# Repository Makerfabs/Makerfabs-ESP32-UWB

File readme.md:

# Makerfabs ESP32 UWB & Display

```c++
/*
Version:		V4.3
Author:			Vincent
Create Date:	2021/11/6
Note:
	2021/12/9 	V2.0:Add a Indoor Positioning demo.
	2022/6/29 	V2.1:Add DW3000 library.
	2022/8/1  	V3.0:Provides a library available for high-power versions. Move DW3000 to other 		  					     repositories.
	2022/9/6	V3.1:Added changes to the high-power version.
	2022/10/26 	V4.0:Add new version with SSD1306
	2022/11/15	V4.1:Change library name to mf_DW1000.zip
	2022/12/29	V4.2: Change wiki link
	2023/1/3	V4.3: Change directory name.
*/
```

[toc]

# Makerfabs

[Makerfabs home page](https://www.makerfabs.com/)

[Makerfabs Wiki](https://wiki.makerfabs.com/)

# Makerfabs ESP32 UWB Serials
## Intruduce

ESP32 UWB : [esp32-uwb-ultra-wideband](https://www.makerfabs.com/esp32-uwb-ultra-wideband.html) 

ESP32 UWB Pro : [esp32-uwb-high-power](https://www.makerfabs.com/esp32-uwb-high-power-120m.html)

ESP32 UWB Pro with Display : [ESP32 UWB Pro with Display](https://www.makerfabs.com/esp32-uwb-pro-with-display.html)

Wiki Link : [ESP32 UWB Pro with Display](https://wiki.makerfabs.com/ESP32_UWB_Pro_with_Display.html) 

Ultra-wideband (UWB) is a short-range, wireless communication protocol that operates through radio waves, enables secure reliable ranging and precision sensing, creating a new dimension of spatial context for wireless devices.

This new ESP32 UWB pro with display is the updated version of ESP32 UWB Pro, with the following new spec:

- On-board OLED, 1.3” 128*64, so the distance results can be directly displayed
- Lipo battery charger& connector, so this module can work separately with batteries
- Update UWB position, so the module can be directly installed into a case

| | **UWB Basic** | **UWB Pro** | **UWB Pro with Display** | **UWB DW3000** |
| --------------------- | ------------------------------------------------------------ | ------------------------------------------------------------ | ------------------------ | ------------------------------------------------------------ |
| CPU                   | ESP32-WROOM/WROVER                                           | ESP32-WROVER                                                 | ESP32-WROVER             | ESP32-WROOM/WROVER                                           |
| Core UWB              | DW1000                                                       | DW1000                                                       | DW1000                   | DW3000                                                       |
| Screen                | N                                                            | N                                                            | Y                        | N                                                            |
| Measuring distance(m) | 45                                                           | 200                                                          | 200                      | 20                                                           |
| Battery Socket        | N                                                            | N                                                            | Y                        | N                                                            |
| UWB Channel           | 2/5                                                          | 2/5                                                          | 2/5                      | 5/9                                                          |
| Apple Interoperable   | N                                                            | N                                                            | N                        | Y                                                            |
| Suitable for          | Normal Testing                                               | Long distance needed                                         | Long distance needed     | Product development                                          |

### UWB Basic

### UWB Pro

### UWB Pro with Display

# Example

## Compiler Options

**If you have any questions，such as how to install the development board, how to download the code, how to install the library. Please refer to :[Makerfabs_FAQ](https://github.com/Makerfabs/Makerfabs_FAQ)**

- Install board : ESP32 .
- Rename mf_DW1000.zip to DW1000.zip and install it.
- Install library : Adafruit_SSD1306
- Upload code, select board "ESP32 DEV"

**This library was modified from the [DW1000](https://github.com/thotro/arduino-dw1000) library to work with the Makerfabs hardware. **

**Please download the latest version from our Github.**

## Example List

### uwb_tag

*For ESP32 UWB and ESP32 UWB Pro*

Distance to the receiving end of the test. You need an anchor point to receive data.

### uwb_tag_display

*For ESP32 UWB Pro with display*

Distance to the receiving end of the test. You need an anchor point to receive data.

### anchor

*For ESP32 UWB and ESP32 UWB Pro*

Distance test anchor point.

### anchor_display

*For ESP32 UWB Pro with display*

Distance test anchor point.

### Indoor positioning

*For ESP32 UWB and ESP32 UWB Pro*

Three UWB modules were used for indoor plane positioning. Data is transmitted through UDP protocol and graphically displayed in Python. 

The law of cosines is used to calculate tag coordinates.

```python
def tag_pos(a, b, c):
    # p = (a + b + c) / 2.0
    # s = cmath.sqrt(p * (p - a) * (p - b) * (p - c))
    # y = 2.0 * s / c
    # x = cmath.sqrt(b * b - y * y)
    cos_a = (b * b + c*c - a * a) / (2 * b * c)
    x = b * cos_a
    y = b * cmath.sqrt(1 - cos_a * cos_a)

    return round(x.real, 1), round(y.real, 1)
```

## Pin Define

### ESP32 UWB and ESP32 UWB Pro

```c++
#define SPI_SCK 18
#define SPI_MISO 19
#define SPI_MOSI 23

#define DW_CS 4
#define PIN_RST 27
#define PIN_IRQ 34
```

### ESP32 Pro with display

```c++
#define SPI_SCK 18
#define SPI_MISO 19
#define SPI_MOSI 23

#define UWB_SS 21   // spi select pin
#define UWB_RST 27  // reset pin
#define UWB_IRQ 34  // irq pin

#define I2C_SDA 4	//I2C screen ssd1306
#define I2C_SCL 5
```

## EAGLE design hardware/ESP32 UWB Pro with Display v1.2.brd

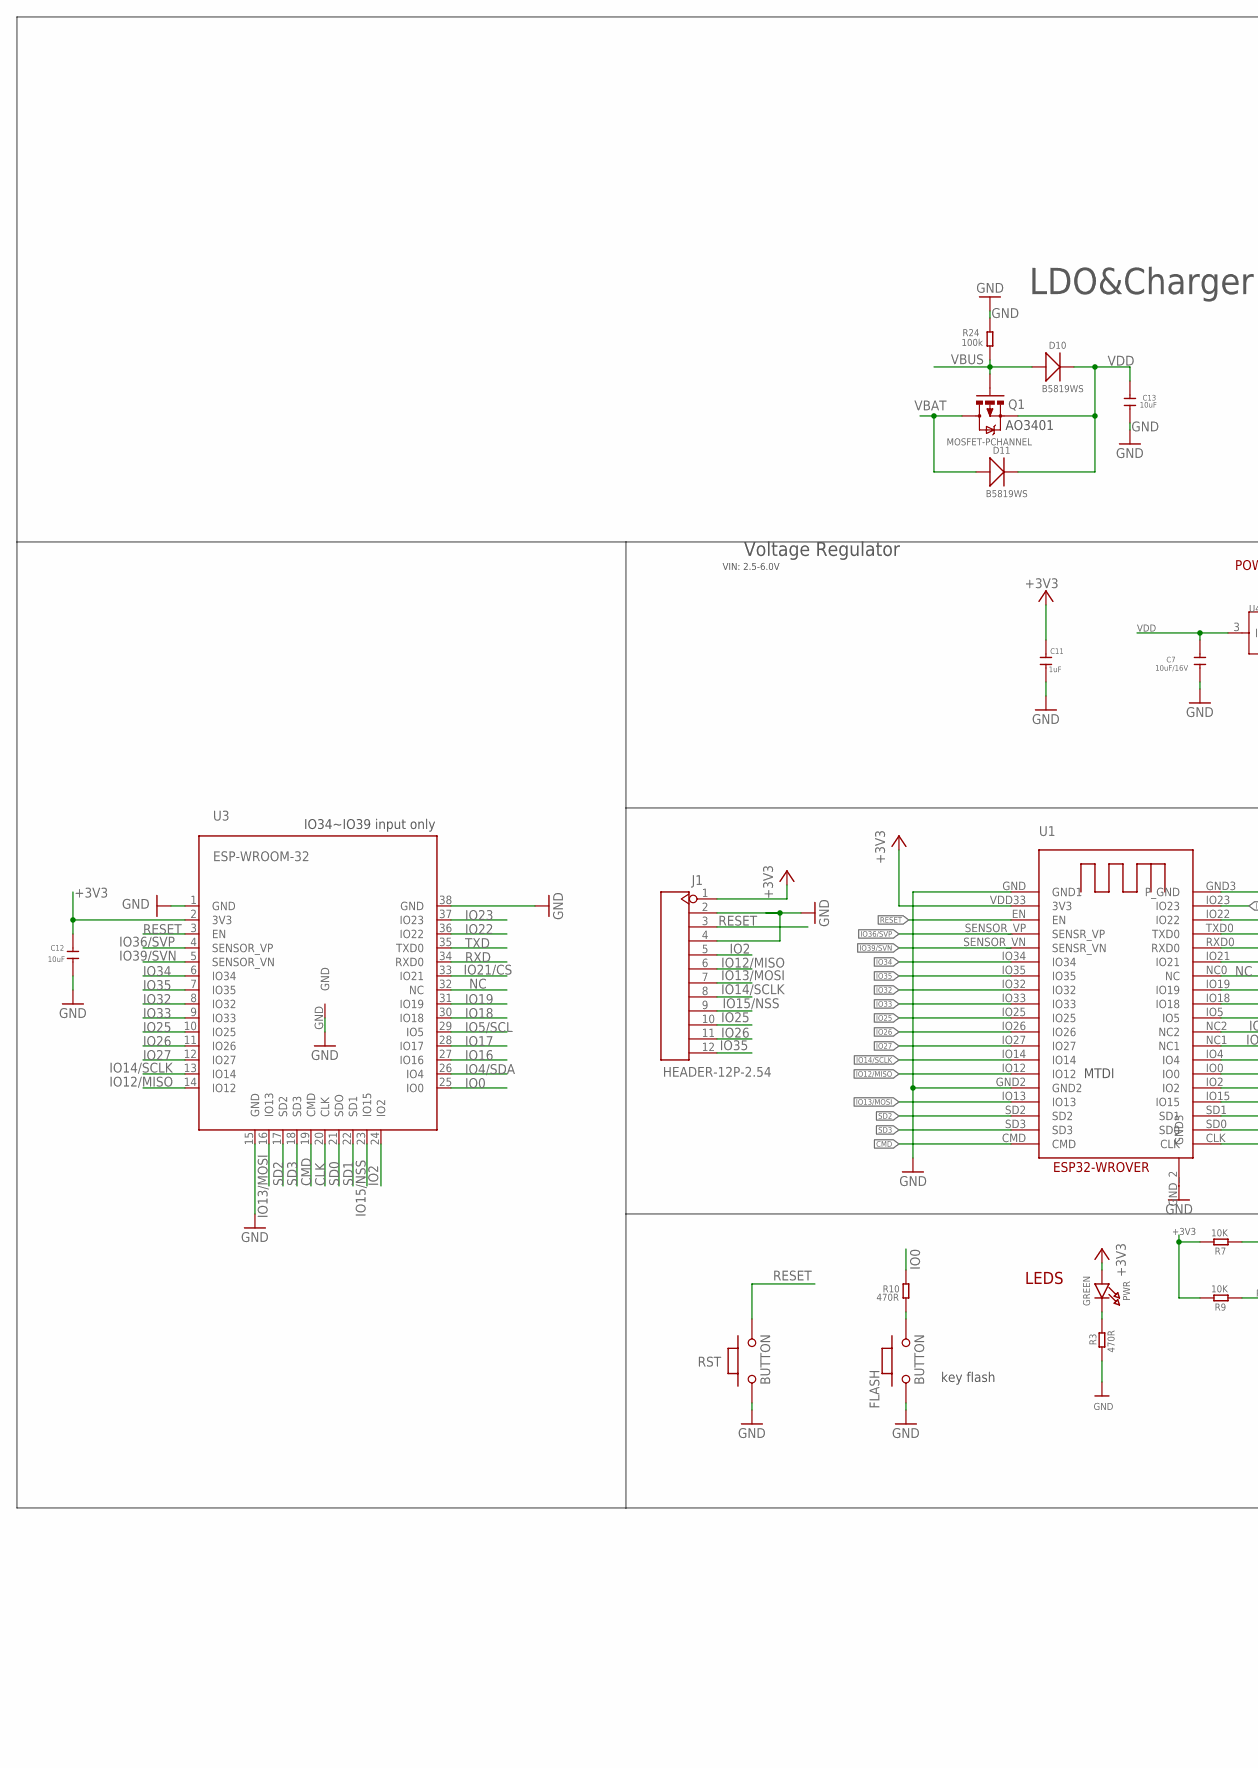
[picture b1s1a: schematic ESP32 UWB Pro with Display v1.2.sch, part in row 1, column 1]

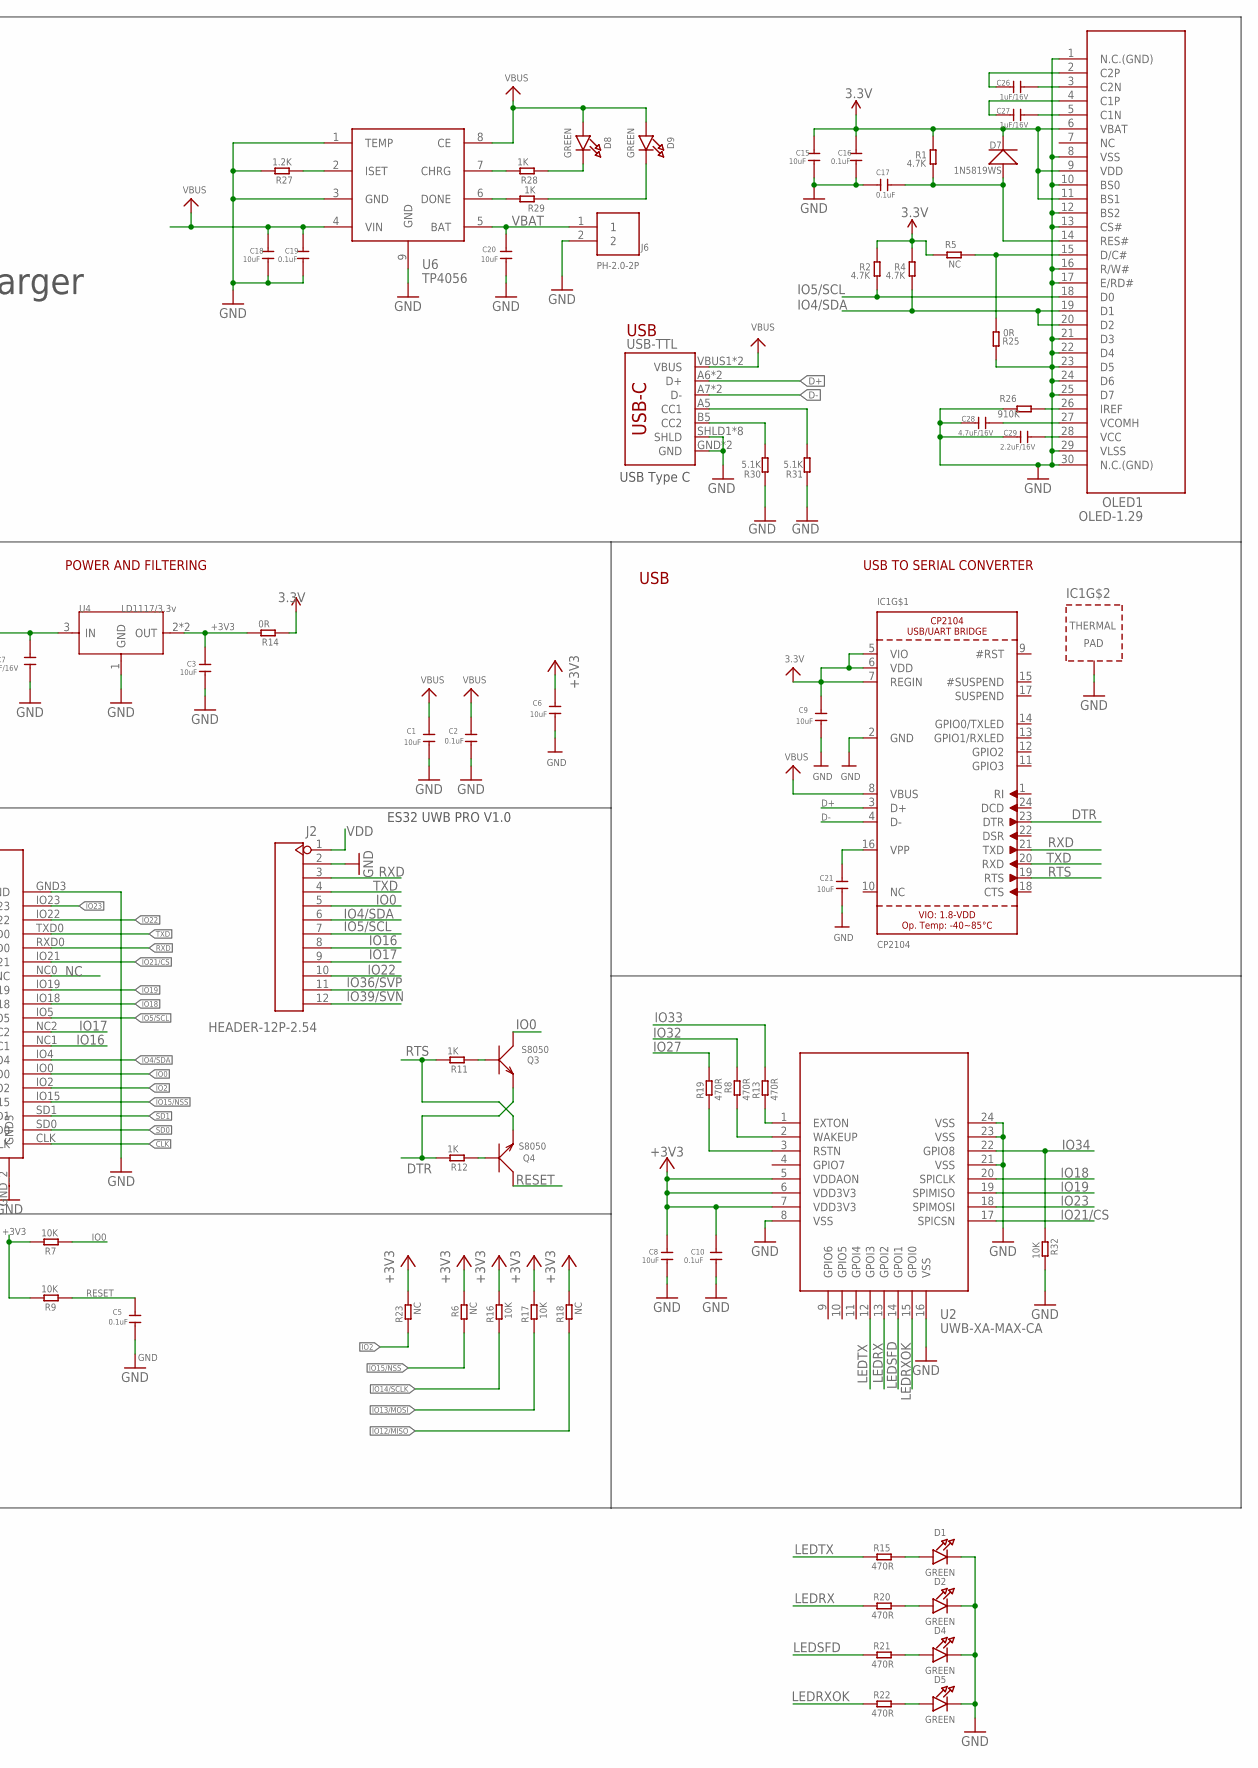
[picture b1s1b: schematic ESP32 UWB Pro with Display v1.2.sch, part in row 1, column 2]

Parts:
C1, C3, C6, C8, C9, C12, C13, C15, C18, C20, C21: 10uF; 0603
C2, C5, C10, C16, C17, C19: 0.1uF; 0603
C7: 10uF/16V; 0603
C11: 1uF; 0603
C26, C27: 1uF/16V; 0603
C28: 4.7uF/16V; 0603
C29: 2.2uF/16V; 0603
D1, D2, D4, D5, D8, D9: GREEN; CHIPLED_0805_NOOUTLINE
D7: 1N5819WS; SOD323
D10, D11: B5819WS; SOD323
FLASH: BUTTON; 157SW
IC1: CP2104; QFN24_4MM_SMSC
J1, J2: HEADER-12P-2.54; 12P-2.54
J6: PH-2.0-2P
OLED1: OLED-1.29
PWR: GREEN; CHIPLED_0805_NOOUTLINE
Q1: MOSFET-PCHANNEL; SOT23-3
Q3, Q4: S8050; SOT23
R1, R2, R4: 4.7K; R0603
R3, R8, R10, R13, R15, R19, R20, R21, R22: 470R; R0603
R5, R6, R18, R23: NC; R0603
R7, R9, R16, R17, R32: 10K; R0603
R11, R12, R28, R29: 1K; R0603
R14, R25: 0R; R0603
R24: 100k; R0603
R26: 910K; R0603
R27: 1.2K; R0603
R30, R31: 5.1K; DISCRETE_R0603
RST: BUTTON; 157SW
U1: ESP32-WROVER
U2: UWB-XA-MAX-CA; UWB-X1-MAK-CA
U3: ESP-WROOM-32
U4: LD1117/3.3v; SOT89
U6: TP4056; SOP8-1.27P
USB-TTL: USB_C5; USB-C-16P-5

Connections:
3.3V: C15.1, C16.1, D7.-, OLED1.6 (VBAT), OLED1.9 (VDD), OLED1.11 (BS1), R1.2, R2.2, R4.2, R5.2, R14.1
+3V3: C3.1, C6.1, C8.1, C9.1, C10.1, C11.1, C12.1, IC1.5 (VIO), IC1.6 (VDD), IC1.7 (REGIN), J1.1, PWR.A, R6.2, R7.2, R9.2, R14.2, R16.2, R17.2, R18.2, R23.2, U1.VDD33 (3V3), U2.5 (VDDAON), U2.6 (VDD3V3), U2.7 (VDD3V3), U3.2 (3V3), U4.2 (OUT), U4.4 (OUT)
CLK: U1.CLK, U3.20 (CLK)
CMD: U1.CMD, U3.19 (CMD)
D+: IC1.3 (D+), USB-TTL.A6 (D+), USB-TTL.B6 (D+)
D-: IC1.4 (D-), USB-TTL.A7 (D-), USB-TTL.B7 (D-)
DTR: IC1.23 (DTR), Q3.2 (E), R12.2
GND: C1.2, C2.2, C3.2, C5.2, C6.2, C7.2, C8.2, C9.2, C10.2, C11.2, C12.2, C13.1, C15.2, C16.2, C17.1, C18.2, C19.2, C20.2, C21.2, C28.1, C29.1, D1.C, D2.C, D4.C, D5.C, FLASH.1, IC1.2 (GND), IC1.THERM (TP), J1.2, J1.4, J2.2, J6.2, OLED1.1 (N.C.(GND)), OLED1.8 (VSS), OLED1.10 (BS0), OLED1.12 (BS2), OLED1.13 (CS#), OLED1.16 (R/W#), OLED1.17 (E/RD#), OLED1.21 (D3), OLED1.22 (D4), OLED1.23 (D5), OLED1.24 (D6), OLED1.25 (D7), OLED1.29 (VLSS), OLED1.30 (N.C.(GND)), R3.1, R24.2, R25.2, R26.2, R27.2, R30.1, R31.1, R32.2, RST.1, U1.GND (GND1), U1.GND2, U1.GND3 (P_GND), U1.GND_2 (GND3), U2.8 (VSS), U2.16 (VSS), U2.21 (VSS), U2.23 (VSS), U2.24 (VSS), U3.1 (GND), U3.15 (GND), U3.38 (GND), U3.GND, U4.1 (GND), U6.1 (TEMP), U6.3 (GND), U6.9 (GND), USB-TTL.GND, USB-TTL.GND2 (GND), USB-TTL.SHLD1 (SHLD), USB-TTL.SHLD2 (SHLD), USB-TTL.SHLD3 (SHLD), USB-TTL.SHLD4 (SHLD), USB-TTL.SHLD5 (SHLD), USB-TTL.SHLD6 (SHLD), USB-TTL.SHLD7 (SHLD), USB-TTL.SHLD8 (SHLD)
IO0: J2.5, Q3.3 (C), R7.1, R10.2, U1.IO0, U3.25 (IO0)
IO2: J1.5, R23.1, U1.IO2, U3.24 (IO2)
IO4/SDA: J2.6, OLED1.19 (D1), OLED1.20 (D2), R4.1, U1.IO4, U3.26 (IO4)
IO5/SCL: J2.7, OLED1.18 (D0), R2.1, U1.IO5, U3.29 (IO5)
IO12/MISO: J1.6, R18.1, U1.IO12, U3.14 (IO12)
IO13/MOSI: J1.7, R17.1, U1.IO13, U3.16 (IO13)
IO14/SCLK: J1.8, R16.1, U1.IO14, U3.13 (IO14)
IO15/NSS: J1.9, R6.1, U1.IO15, U3.23 (IO15)
IO16: J2.8, U1.NC1, U3.27 (IO16)
IO17: J2.9, U1.NC2, U3.28 (IO17)
IO18: U1.IO18, U2.20 (SPICLK), U3.30 (IO18)
IO19: U1.IO19, U2.19 (SPIMISO), U3.31 (IO19)
IO21/CS: U1.IO21, U2.17 (SPICSN), U3.33 (IO21)
IO22: J2.10, U1.IO22, U3.36 (IO22)
IO23: U1.IO23, U2.18 (SPIMOSI), U3.37 (IO23)
IO25: J1.10, U1.IO25, U3.10 (IO25)
IO26: J1.11, U1.IO26, U3.11 (IO26)
IO27: R19.2, U1.IO27, U3.12 (IO27)
IO32: R8.2, U1.IO32, U3.8 (IO32)
IO33: R13.2, U1.IO33, U3.9 (IO33)
IO34: R32.1, U1.IO34, U2.22 (GPIO8), U3.6 (IO34)
IO35: J1.12, U1.IO35, U3.7 (IO35)
IO36/SVP: J2.11, U1.SENSOR_VP (SENSR_VP), U3.4 (SENSOR_VP)
IO39/SVN: J2.12, U1.SENSOR_VN (SENSR_VN), U3.5 (SENSOR_VN)
LEDRX: R20.1, U2.13 (GPOI2)
LEDRXOK: R22.1, U2.15 (GPOI0)
LEDSFD: R21.1, U2.14 (GPOI1)
LEDTX: R15.1, U2.12 (GPOI3)
unnamed: D1.A, R15.2
unnamed: C21.1, IC1.16 (VPP)
unnamed: C17.2, D7.+, OLED1.14 (RES#), R1.1
unnamed: OLED1.15 (D/C#), R5.1, R25.1
unnamed: PWR.C, R3.2
unnamed: C28.2, OLED1.27 (VCOMH)
unnamed: C26.2, OLED1.3 (C2N)
unnamed: C29.2, OLED1.28 (VCC)
unnamed: OLED1.26 (IREF), R26.1
unnamed: R13.1, U2.1 (EXTON)
unnamed: R8.1, U2.2 (WAKEUP)
unnamed: R19.1, U2.3 (RSTN)
unnamed: Q4.1 (B), R12.1
unnamed: Q3.1 (B), R11.1
unnamed: FLASH.2, R10.1
unnamed: D2.A, R20.2
unnamed: D4.A, R21.2
unnamed: D5.A, R22.2
unnamed: C26.1, OLED1.2 (C2P)
unnamed: C27.1, OLED1.4 (C1P)
unnamed: C27.2, OLED1.5 (C1N)
unnamed: R27.1, U6.2 (ISET)
unnamed: R31.2, USB-TTL.A5 (CC1)
unnamed: R30.2, USB-TTL.B5 (CC2)
unnamed: R28.2, U6.7 (CHRG)
unnamed: R29.2, U6.6 (DONE)
unnamed: D8.C, R28.1
unnamed: D9.C, R29.1
NC: U1.NC0 (NC), U3.32 (NC)
RESET: C5.1, J1.3, Q4.3 (C), R9.1, RST.2, U1.EN, U3.3 (EN)
RTS: IC1.19 (RTS), Q4.2 (E), R11.2
RXD: IC1.21 (TXD), J2.3, U1.RXD0, U3.34 (RXD0)
SD0: U1.SD0, U3.21 (SDO)
SD1: U1.SD1, U3.22 (SD1)
SD2: U1.SD2, U3.17 (SD2)
SD3: U1.SD3, U3.18 (SD3)
TXD: IC1.20 (RXD), J2.4, U1.TXD0, U3.35 (TXD0)
VBAT: C20.1, D11.+, J6.1, Q1.3 (D), U6.5 (BAT)
VBUS: C1.1, C2.1, C18.1, C19.1, D8.A, D9.A, D10.+, IC1.8 (VBUS), Q1.1 (G), R24.1, U6.4 (VIN), U6.8 (CE), USB-TTL.VBUS1 (VBUS), USB-TTL.VBUS2 (VBUS)
VDD: C7.1, C13.2, D10.-, D11.-, J2.1, Q1.2 (S), U4.3 (IN)

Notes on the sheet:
USB
LEDS
POWER AND FILTERING
USB TO SERIAL CONVERTER
key flash
ES32 UWB PRO V1.0
MTDI
IO34~IO39 input only
Voltage Regulator
VIN: 2.5-6.0V
USB Type C
LDO&Charger
AO3401

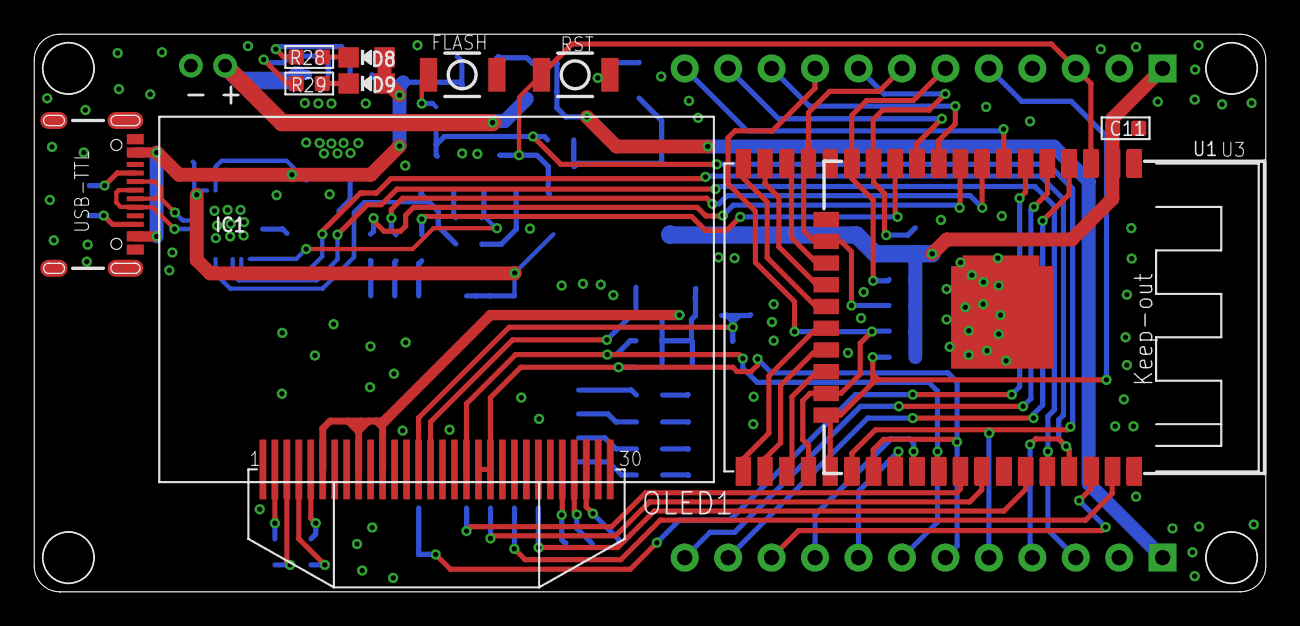
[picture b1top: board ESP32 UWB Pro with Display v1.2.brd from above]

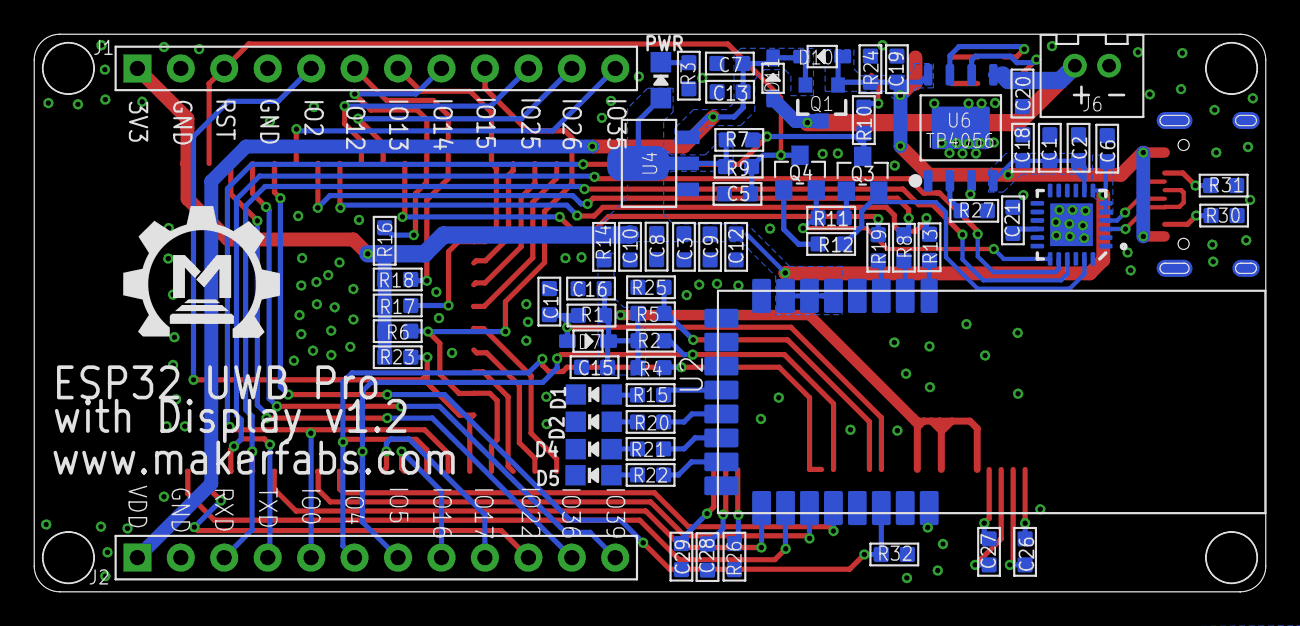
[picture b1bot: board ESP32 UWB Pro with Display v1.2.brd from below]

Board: 2 copper layers, 72.0 x 32.6 mm, 82 parts (71 on the bottom side), 76 nets.

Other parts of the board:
U$1: MAKERFABS_0.3

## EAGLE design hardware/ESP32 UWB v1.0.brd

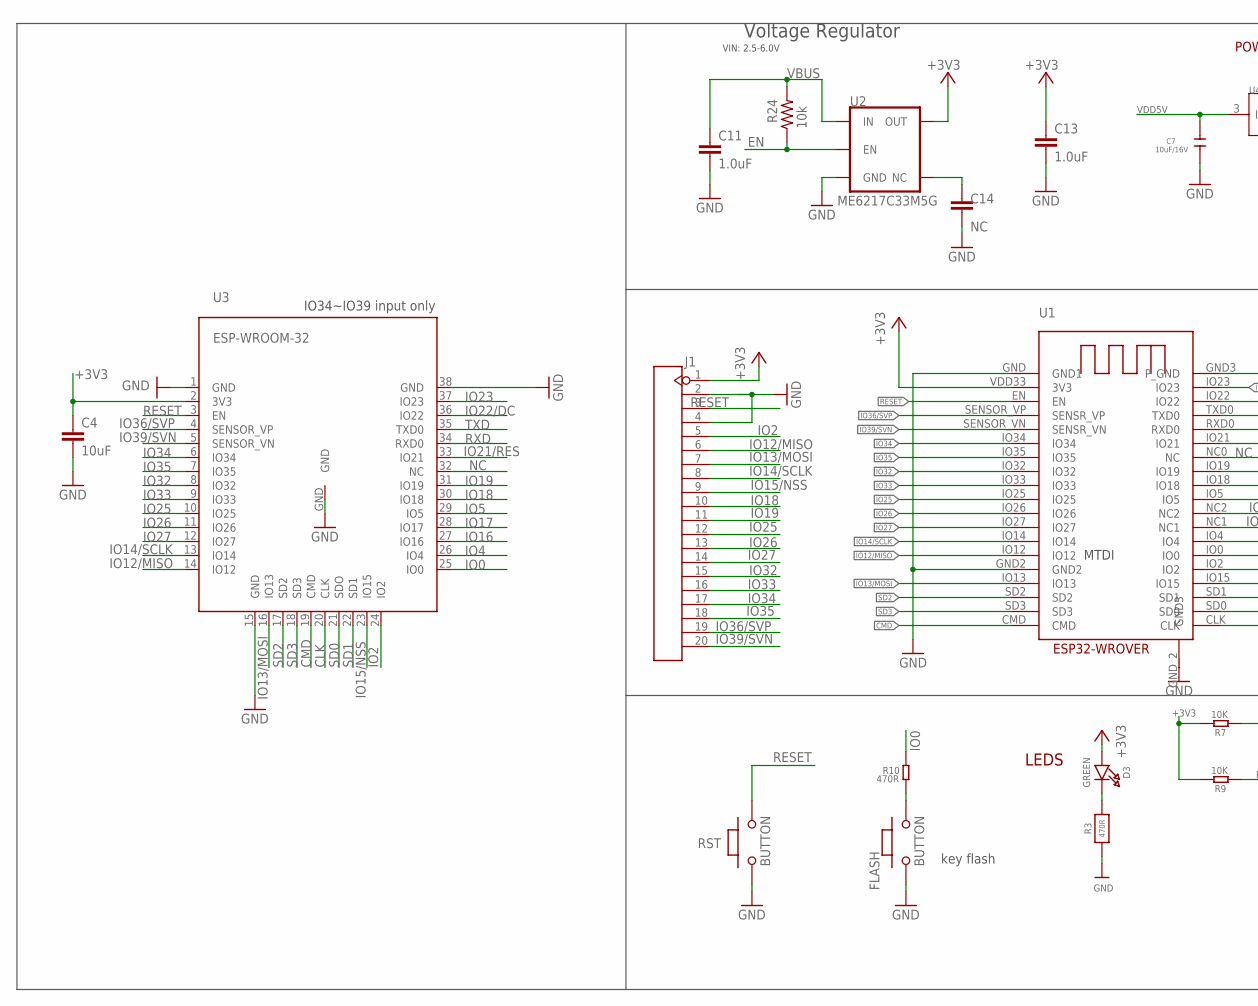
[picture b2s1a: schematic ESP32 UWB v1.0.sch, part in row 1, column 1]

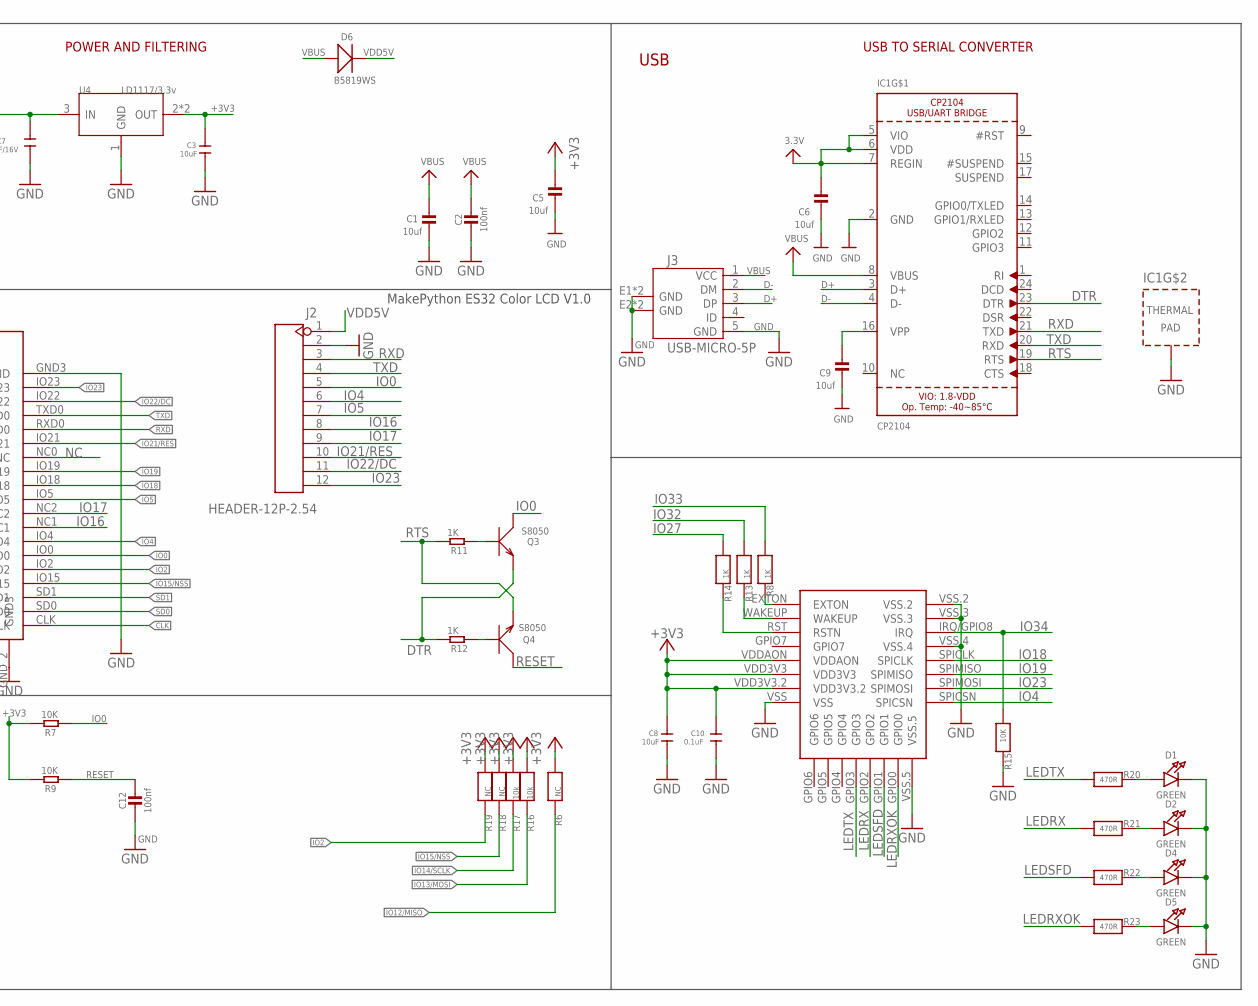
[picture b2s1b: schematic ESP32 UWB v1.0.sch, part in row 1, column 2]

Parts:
C1, C5, C6, C9: 10uf; 0603-NO
C2, C12: 100nf; 0603-NO
C3, C4, C8: 10uF; C0603
C7: 10uF/16V; C0603
C10: 0.1uF; C0603
C11, C13: 1.0uF; 0603
C14: NC; 0603
D1, D2, D3, D4, D5: GREEN; CHIPLED_0805_NOOUTLINE
D6: B5819WS; SOD323
FLASH: BUTTON; 157SW
IC1: CP2104; QFN24_4MM_SMSC
J1: HEADER-20P-2.54; 20P-2.54
J2: HEADER-12P-2.54; 12P-2.54
J3: USB-MICRO-5P; MICRO-USB-5P
Q3, Q4: S8050; SOT23
R3, R20, R21, R22, R23: 470R; 0603-NO
R6, R18, R19: NC; 0603-NO
R7, R9: 10K; 0603
R8, R13, R14: 1K; 0603-NO
R10: 470R; 0603
R11, R12: 1K; 0603
R15: 10K; 0603-NO
R16, R17: 10k; 0603-NO
R24: 10k; 0603
RST: BUTTON; 157SW
U1: ESP32-WROVER
U2: ME6217C33M5G; SOT23-5
U3: ESP-WROOM-32
U4: LD1117/3.3v; SOT89
U5: DWM1000

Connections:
+3V3: C3.1, C4.1, C5.1, C6.1, C8.1, C10.1, C13.1, D3.A, IC1.5 (VIO), IC1.6 (VDD), IC1.7 (REGIN), J1.1, R6.1, R7.2, R9.2, R16.1, R17.1, R18.1, R19.1, U1.VDD33 (3V3), U2.5 (OUT), U3.2 (3V3), U4.2 (OUT), U4.4 (OUT), U5.VDD3V3, U5.VDD3V3.2, U5.VDDAON
CLK: U1.CLK, U3.20 (CLK)
CMD: U1.CMD, U3.19 (CMD)
D+: IC1.3 (D+), J3.3 (DP)
D-: IC1.4 (D-), J3.2 (DM)
DTR: IC1.23 (DTR), Q3.2 (E), R12.2
EN: R24.1, U2.3 (EN)
GND: C1.2, C2.2, C3.2, C4.2, C5.2, C6.2, C7.2, C8.2, C9.2, C10.2, C11.2, C12.2, C13.2, C14.2, D1.C, D2.C, D4.C, D5.C, FLASH.1, IC1.2 (GND), IC1.THERM (TP), J1.2, J1.4, J2.2, J3.5 (GND), J3.E1 (GND), J3.E2 (GND), J3.P1 (GND), J3.P2 (GND), R3.1, R15.2, RST.1, U1.GND (GND1), U1.GND2, U1.GND3 (P_GND), U1.GND_2 (GND3), U2.2 (GND), U3.1 (GND), U3.15 (GND), U3.38 (GND), U3.GND, U4.1 (GND), U5.VSS, U5.VSS.2, U5.VSS.3, U5.VSS.4, U5.VSS.5
IO0: J2.5, Q3.3 (C), R7.1, R10.2, U1.IO0, U3.25 (IO0)
IO2: J1.5, R19.2, U1.IO2, U3.24 (IO2)
IO4: J2.6, U1.IO4, U3.26 (IO4), U5.SPICSN
IO5: J2.7, U1.IO5, U3.29 (IO5)
IO12/MISO: J1.6, R6.2, U1.IO12, U3.14 (IO12)
IO13/MOSI: J1.7, R16.2, U1.IO13, U3.16 (IO13)
IO14/SCLK: J1.8, R17.2, U1.IO14, U3.13 (IO14)
IO15/NSS: J1.9, R18.2, U1.IO15, U3.23 (IO15)
IO16: J2.8, U1.NC1, U3.27 (IO16)
IO17: J2.9, U1.NC2, U3.28 (IO17)
IO18: J1.10, U1.IO18, U3.30 (IO18), U5.SPICLK
IO19: J1.11, U1.IO19, U3.31 (IO19), U5.SPIMISO
IO21/RES: J2.10, U1.IO21, U3.33 (IO21)
IO22/DC: J2.11, U1.IO22, U3.36 (IO22)
IO23: J2.12, U1.IO23, U3.37 (IO23), U5.SPIMOSI
IO25: J1.12, U1.IO25, U3.10 (IO25)
IO26: J1.13, U1.IO26, U3.11 (IO26)
IO27: J1.14, R14.1, U1.IO27, U3.12 (IO27)
IO32: J1.15, R13.1, U1.IO32, U3.8 (IO32)
IO33: J1.16, R8.1, U1.IO33, U3.9 (IO33)
IO34: J1.17, R15.1, U1.IO34, U3.6 (IO34), U5.IRQ/GPIO8 (IRQ)
IO35: J1.18, U1.IO35, U3.7 (IO35)
IO36/SVP: J1.19, U1.SENSOR_VP (SENSR_VP), U3.4 (SENSOR_VP)
IO39/SVN: J1.20, U1.SENSOR_VN (SENSR_VN), U3.5 (SENSOR_VN)
LEDRX: R21.1, U5.GPIO2
LEDRXOK: R23.1, U5.GPIO0
LEDSFD: R22.1, U5.GPIO1
LEDTX: R20.1, U5.GPIO3
unnamed: D1.A, R20.2
unnamed: C9.1, IC1.16 (VPP)
unnamed: C14.1, U2.4 (NC)
unnamed: D3.C, R3.2
unnamed: R8.2, U5.EXTON
unnamed: R13.2, U5.WAKEUP
unnamed: R14.2, U5.RST (RSTN)
unnamed: Q4.1 (B), R12.1
unnamed: Q3.1 (B), R11.1
unnamed: FLASH.2, R10.1
unnamed: D2.A, R21.2
unnamed: D4.A, R22.2
unnamed: D5.A, R23.2
NC: U1.NC0 (NC), U3.32 (NC)
RESET: C12.1, J1.3, Q4.3 (C), R9.1, RST.2, U1.EN, U3.3 (EN)
RTS: IC1.19 (RTS), Q4.2 (E), R11.2
RXD: IC1.21 (TXD), J2.3, U1.RXD0, U3.34 (RXD0)
SD0: U1.SD0, U3.21 (SDO)
SD1: U1.SD1, U3.22 (SD1)
SD2: U1.SD2, U3.17 (SD2)
SD3: U1.SD3, U3.18 (SD3)
TXD: IC1.20 (RXD), J2.4, U1.TXD0, U3.35 (TXD0)
VBUS: C1.1, C2.1, C11.1, D6.+, IC1.8 (VBUS), J3.1 (VCC), R24.2, U2.1 (IN)
VDD5V: C7.1, D6.-, J2.1, U4.3 (IN)

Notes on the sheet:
USB
LEDS
POWER AND FILTERING
USB TO SERIAL CONVERTER
key flash
MakePython ES32 Color LCD V1.0
MTDI
IO34~IO39 input only
Voltage Regulator
VIN: 2.5-6.0V

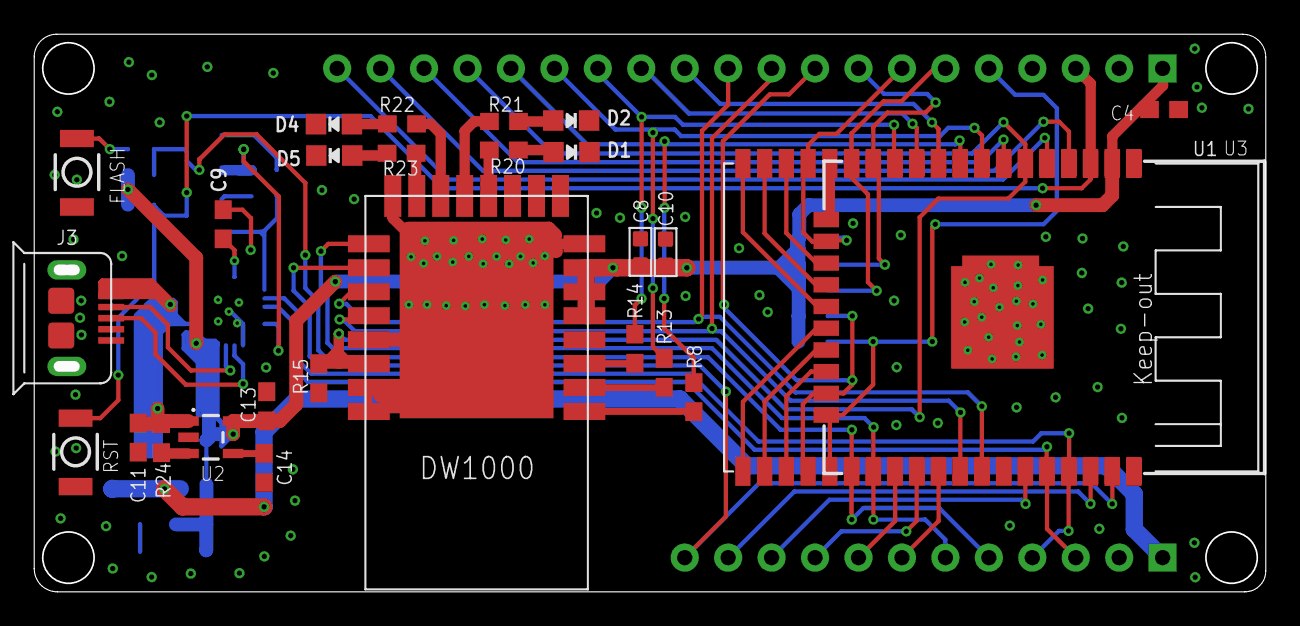
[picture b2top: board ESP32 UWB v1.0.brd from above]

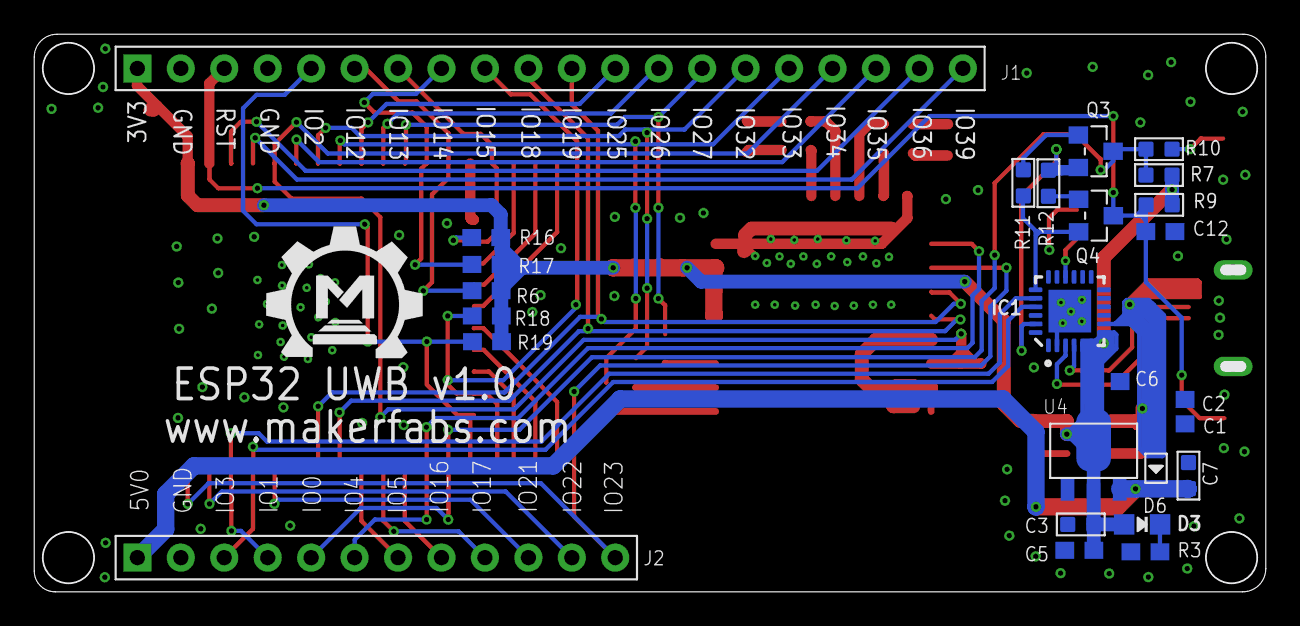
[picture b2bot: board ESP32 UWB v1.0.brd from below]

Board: 2 copper layers, 72.0 x 32.6 mm, 54 parts (27 on the bottom side), 60 nets.

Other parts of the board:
U$1: MAKERFABS_0.3

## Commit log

2021-11-06 Create
2021-11-12 bug fix
2021-12-09 Add indoor position demo
2021-12-10 add pic
2022-06-29 V2.1 add dw3000 lib
2022-08-01 V3.0 Add long range version
2022-09-07 V3.1
2022-10-26 V4.0
2022-10-26 ESP32 UWB Pro with Display v1.2
    hardware
2022-11-15 Rename Library
2022-12-29 Change Wiki Link
2023-01-03 Edit directory name
2023-01-12 Add outdoor positioning demo
2023-03-06 Fix pin set
2023-10-13 Add PDF of sch

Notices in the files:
parts and their libraries:
microbuilder: This work is placed in the public domain, and may be freely used for commercial and non-commercial work with the following conditions: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
User-Submitted: Licensing: Creative Commons ShareAlike 4.0 International - https://creativecommons.org/licenses/by-sa/4.0
